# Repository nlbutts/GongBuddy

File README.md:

# GongBuddy

LoRa radio transmitter with accel/gyro to detect impacts on a gong

DIO5 = ModeReady
DIO4 = CadDetected
DIO3 = CadDone
DIO2 = FhssChangeChannel
DIO1 = RxTimeout
DIO0 = RxDone

Mapping of DIO to the LEDs
DIO3 = CadDone
DIO4 = CadDetected
DIO0 = RxDone
DIO1 = RxTimeout
DIO2 = FhssChangeChannel
DIO5 = ModeReady

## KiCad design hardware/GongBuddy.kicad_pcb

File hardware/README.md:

Designed for this enclosure
https://www.hammfg.com/electronics/small-case/extruded/1455
1455D601BK

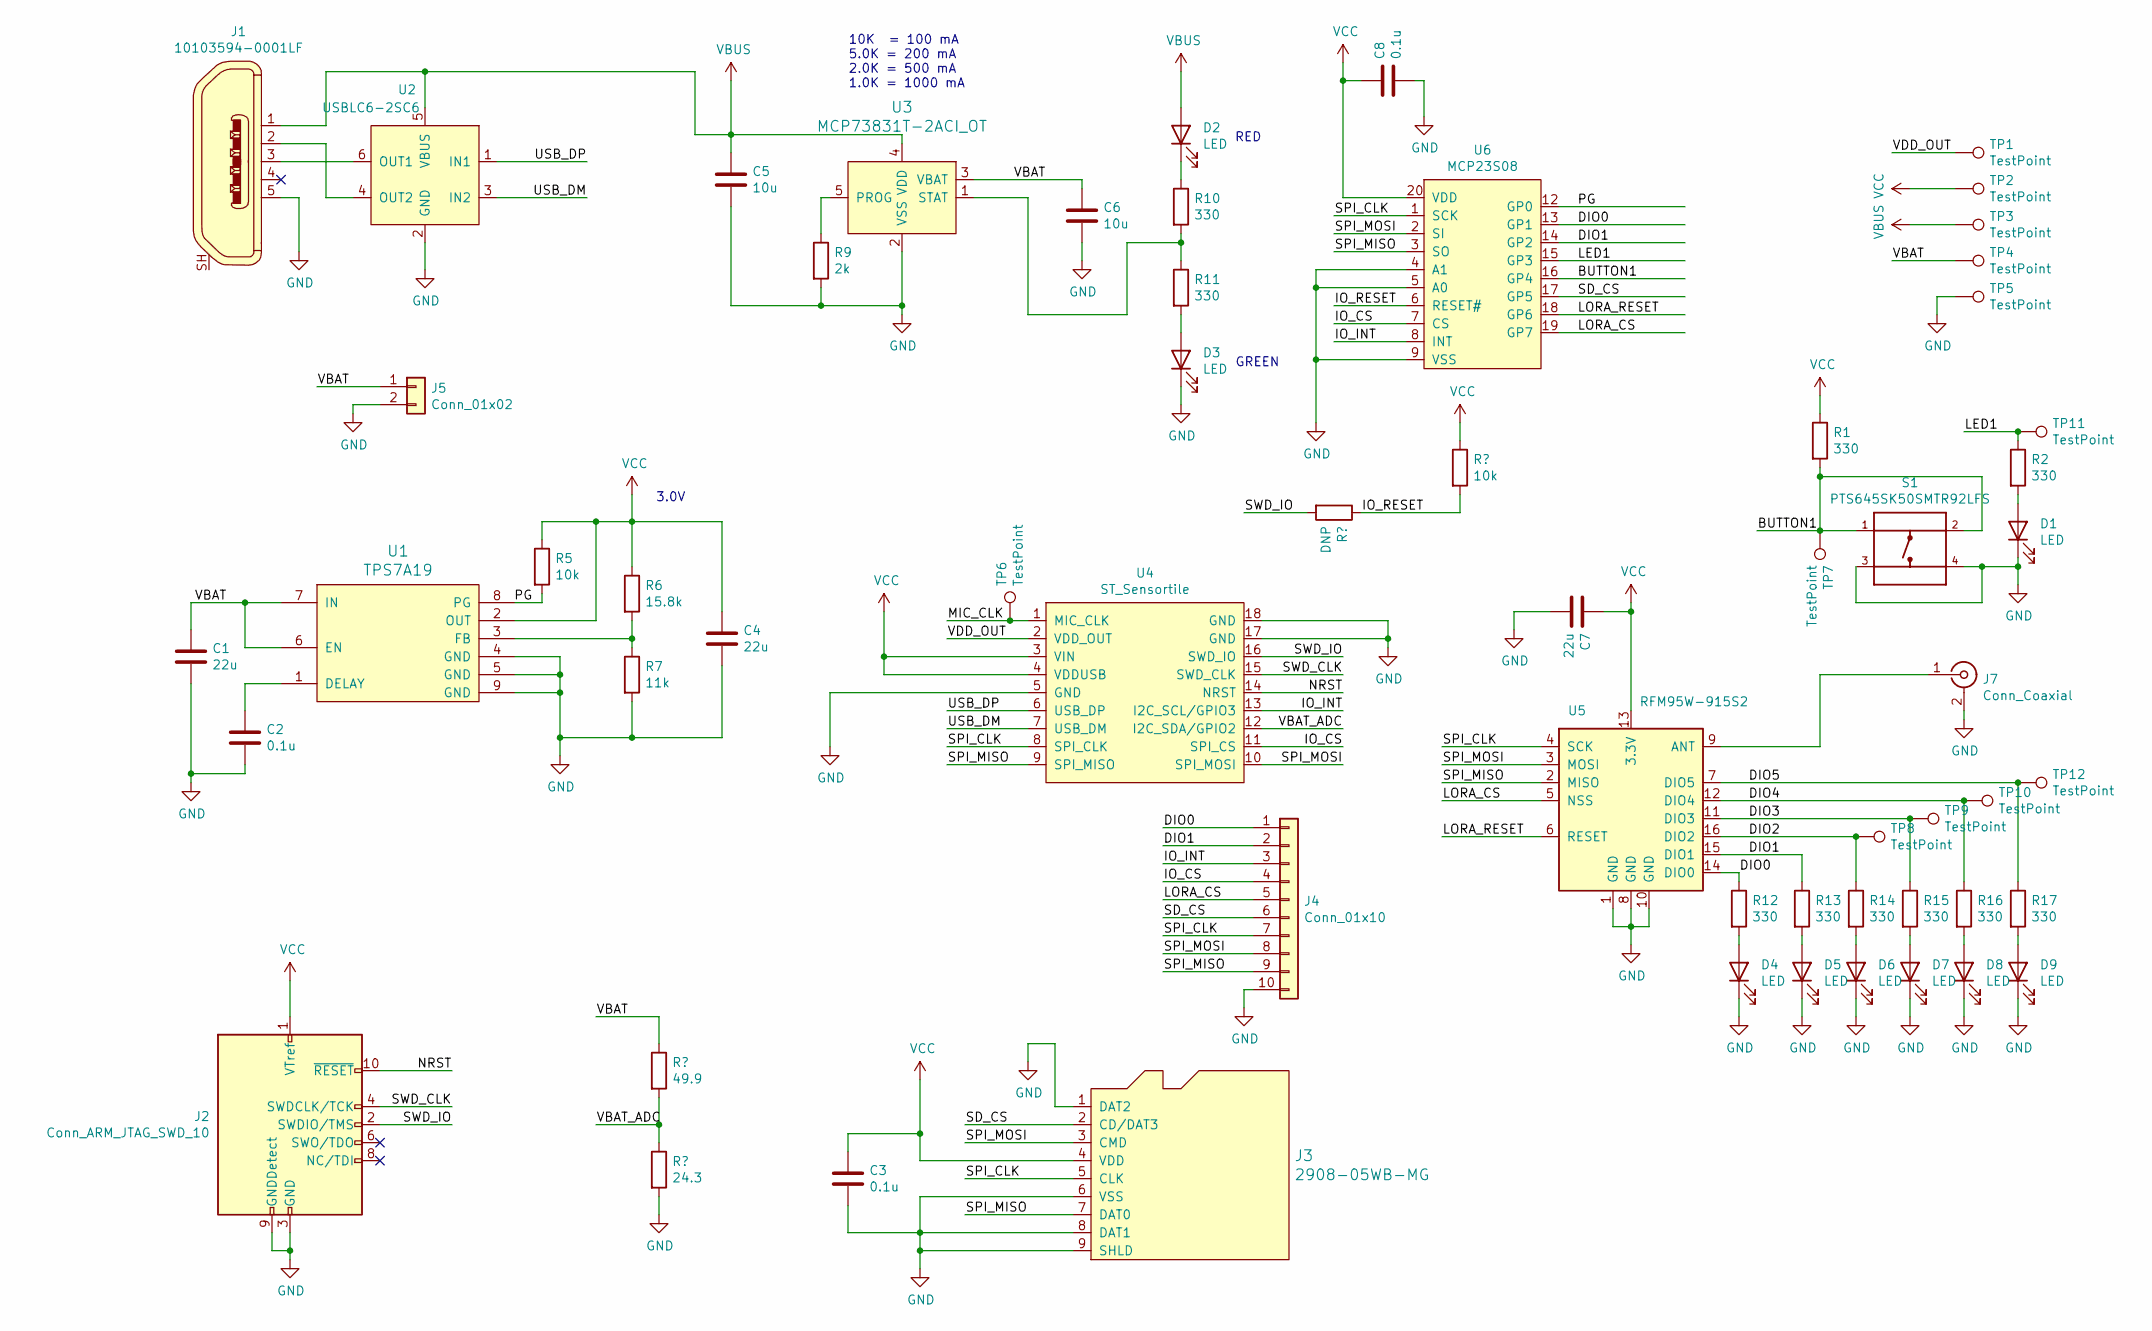
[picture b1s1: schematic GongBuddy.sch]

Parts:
C1, C4: 22u; C_1206_3216Metric
C2, C3, C8: 0.1u; C_0603_1608Metric
C5, C6: 10u; C_0603_1608Metric
C7: 22u; C_0603_1608Metric
D1, D2, D3, D4, D5, D6, D7, D8, D9: LED; LED_0603_1608Metric
J1: 10103594-0001LF; USB_Micro_B_Female_10103594-0001LF; MPN 10103594-0001LF; Digi-Key_PN 609-4050-1-ND
J2: Conn_ARM_JTAG_SWD_10; CortexSWD
J3: 2908-05WB-MG; MicroSD_2908-05WB-MG; MPN 2908-05WB-MG; Digi-Key_PN 3M5607CT-ND
J4: Conn_01x10; PinHeader_1x10_P2.54mm_Vertical
J5: Conn_01x02; JST_PH_B2B-PH-K_1x02_P2.00mm_Vertical
J7: Conn_Coaxial; SAMTEC_SMA-J-P-H-ST-EM1
R1, R2, R10, R11, R12, R13, R14, R15, R16, R17: 330; R_0603_1608Metric
R5: 10k; R_0603_1608Metric
R6: 15.8k; R_0603_1608Metric
R7: 11k; R_0603_1608Metric
R9: 2k; R_0603_1608Metric
S1: PTS645SK50SMTR92LFS; SW_PTS645SK50SMTR92LFS
TP1, TP2, TP3, TP4, TP5, TP6, TP7, TP8, TP9, TP10, TP11, TP12: TestPoint; TestPoint_Pad_D1.0mm
U1: TPS7A19; IC_DRV8601DRBT
U2: USBLC6-2SC6; SOT-23-6; Digikey 497-5235-2-ND
U3: MCP73831T-2ACI_OT; SOT-753; MPN MCP73831T-2ACI/OT; Digi-Key_PN MCP73831T-2ACI/OTCT-ND
U4: ST_Sensortile
U5: RFM95W-915S2; XCVR_RFM95W-915S2
U6: MCP23S08; SSOP-20_5.3x7.2mm_P0.65mm

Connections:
/BUTTON1: R1.2, S1.1, S1.2, TP7.1, U6.16 (GP4); also elsewhere on the board
/DIO0: J4.1, R12.1, U5.14 (DIO0), U6.13 (GP1)
/DIO1: J4.2, R13.1, U5.15 (DIO1), U6.14 (GP2)
/DIO2: R14.1, TP8.1, U5.16 (DIO2)
/DIO3: R15.1, TP9.1, U5.11 (DIO3)
/DIO4: R16.1, TP10.1, U5.12 (DIO4)
/DIO5: R17.1, TP12.1, U5.7 (DIO5)
/IO_CS: J4.4, U4.11 (SPI_CS), U6.7 (CS)
/IO_INT: J4.3, U4.13 (I2C_SCL/GPIO3), U6.8 (INT)
/IO_RESET: U6.6 (RESET#); also elsewhere on the board
/LED1: R2.1, TP11.1, U6.15 (GP3)
/LORA_CS: J4.5, U5.5 (NSS), U6.19 (GP7)
/LORA_RESET: U5.6 (RESET), U6.18 (GP6)
/MIC_CLK: TP6.1, U4.1 (MIC_CLK)
/NRST: J2.10 (~RESET~), U4.14 (NRST)
/PG: R5.2, U1.8 (PG), U6.12 (GP0)
/SD_CS: J3.2 (CD/DAT3), J4.6, U6.17 (GP5)
/SPI_CLK: J3.5 (CLK), J4.7, U4.8 (SPI_CLK), U5.4 (SCK), U6.1 (SCK)
/SPI_MISO: J3.7 (DAT0), J4.9, U4.9 (SPI_MISO), U5.2 (MISO), U6.3 (SO)
/SPI_MOSI: J3.3 (CMD), J4.8, U4.10 (SPI_MOSI), U5.3 (MOSI), U6.2 (SI)
/SWD_CLK: J2.4 (SWDCLK/TCK), U4.15 (SWD_CLK)
/SWD_IO: J2.2 (SWDIO/TMS), U4.16 (SWD_IO); also elsewhere on the board
/USB_DM: U2.3 (IN2), U4.7 (USB_DM)
/USB_DP: U2.1 (IN1), U4.6 (USB_DP)
/VBAT: C1.1, C6.1, J5.1, TP4.1, U1.6 (EN), U1.7 (IN), U3.3 (VBAT); also elsewhere on the board
/VBAT_ADC: U4.12 (I2C_SDA/GPIO2); also elsewhere on the board
GND: C1.2, C2.2, C3.2, C4.2, C5.2, C6.2, C7.2, C8.2, D1.1 (K), D3.1 (K), D4.1 (K), D5.1 (K), D6.1 (K), D7.1 (K), D8.1 (K), D9.1 (K), J1.5, J2.3 (GND), J2.5 (GND), J2.9 (GNDDetect), J3.1 (DAT2), J3.6 (VSS), J3.8 (DAT1), J3.9 (SHLD), J4.10, J5.2, J7.2 (Ext), R7.2, R9.2, S1.3, S1.4, TP5.1, U1.4 (GND), U1.5 (GND), U1.9 (GND), U1.10, U1.11, U1.12, U1.13, U2.2 (GND), U3.2 (VSS), U4.5 (GND), U4.17 (GND), U4.18 (GND), U5.1 (GND), U5.8 (GND), U5.10 (GND), U6.4 (A1), U6.5 (A0), U6.9 (VSS); also elsewhere on the board
unnamed: C2.1, U1.1 (DELAY)
unnamed: D1.2 (A), R2.2
unnamed: D2.1 (K), R10.1
unnamed: D3.2 (A), R11.2
unnamed: D4.2 (A), R12.2
unnamed: D5.2 (A), R13.2
unnamed: D6.2 (A), R14.2
unnamed: D7.2 (A), R15.2
unnamed: D8.2 (A), R16.2
unnamed: D9.2 (A), R17.2
unnamed: J1.2, U2.4 (OUT2)
unnamed: J1.3, U2.6 (OUT1)
unnamed: J7.1 (In), U5.9 (ANT)
unnamed: R6.2, R7.1, U1.3 (FB)
unnamed: R9.1, U3.5 (PROG)
unnamed: R10.2, R11.1, U3.1 (STAT)
VBUS: C5.1, D2.2 (A), J1.1, TP3.1, U2.5 (VBUS), U3.4 (VDD)

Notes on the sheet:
10K = 100 mA 5.0K = 200 mA 2.0K = 500 mA 1.0K = 1000 mA
RED
GREEN
3.0V

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
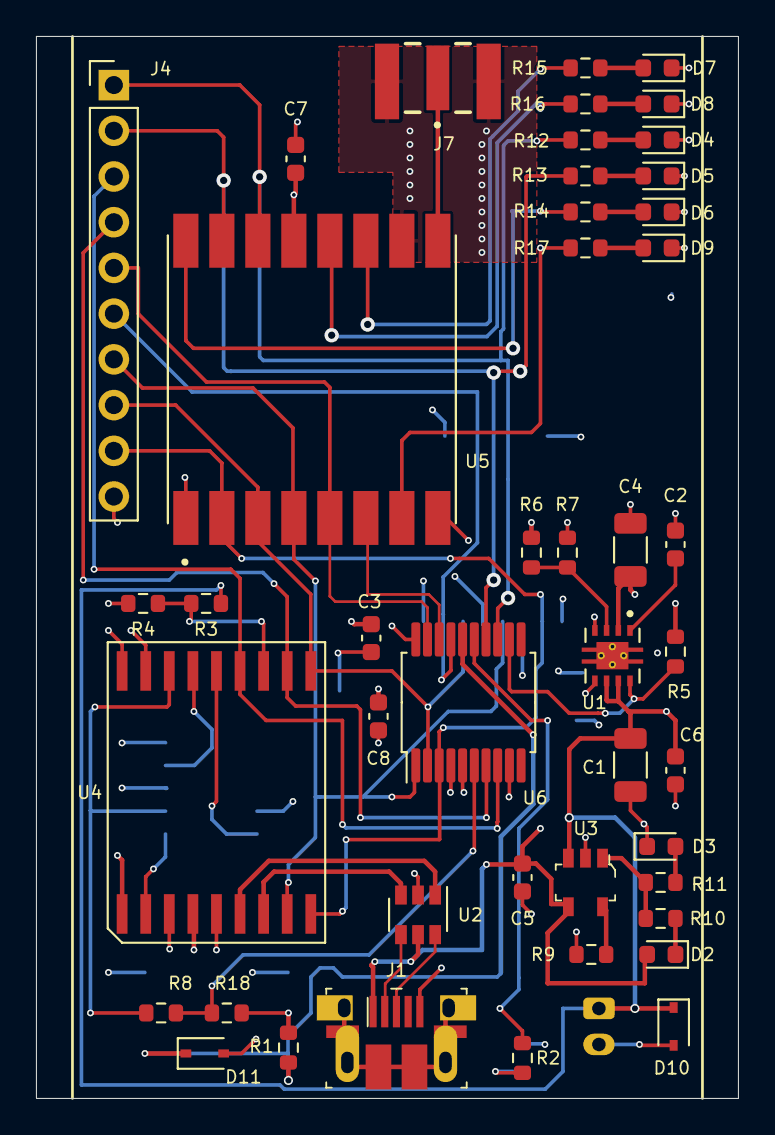
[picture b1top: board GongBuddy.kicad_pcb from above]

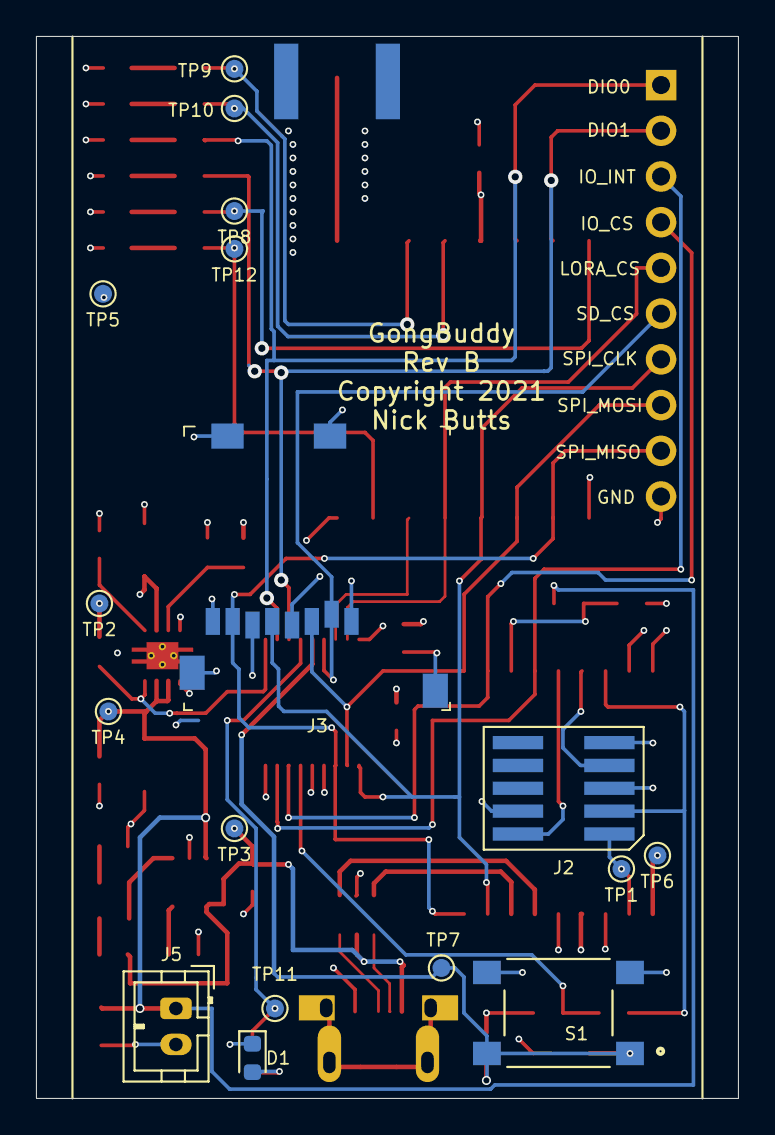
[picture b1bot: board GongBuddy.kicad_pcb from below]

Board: 4 copper layers, 39.0 x 59.0 mm, 62 parts (17 on the bottom side), 46 nets.

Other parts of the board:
D10, D11: DESD5V0U1BA-7; D_SOD-323
R3: 49.9; R_0603_1608Metric
R4: 24.3; R_0603_1608Metric
R8: DNP; R_0603_1608Metric
R18: 10k; R_0603_1608Metric

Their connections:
/BUTTON1: D11.1; also elsewhere on the board
/IO_RESET: R8.1, R18.2; also elsewhere on the board
/SWD_IO: R8.2; also elsewhere on the board
/VBAT: D10.1, R3.1; also elsewhere on the board
/VBAT_ADC: R3.2, R4.1; also elsewhere on the board
GND: D10.2, D11.2, R4.2; also elsewhere on the board

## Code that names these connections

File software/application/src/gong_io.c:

#include <stdint.h>
#include "mcp23S08.h"
#include "main.h"

#define IO_PG           0x01
#define IO_DIO0         0x02
#define IO_DIO1         0x04
#define IO_LED          0x08
#define IO_BUTTON       0x10
#define IO_SD_CS        0x20
#define IO_LORA_RESET   0x40
#define IO_LORA_CS      0x80

static void   *_spi;

static int write_spi(uint8_t * data, uint8_t len)
{
    HAL_GPIO_WritePin(IO_CS_GPIO_Port, IO_CS_Pin, 0);
    HAL_SPI_Transmit(_spi, data, len, 1000);
    HAL_GPIO_WritePin(IO_CS_GPIO_Port, IO_CS_Pin, 1);
    return 0;
}

static int tx_rx_spi(uint8_t * txdata, uint8_t * rxdata, uint8_t len)
{
    HAL_GPIO_WritePin(IO_CS_GPIO_Port, IO_CS_Pin, 0);
    HAL_SPI_TransmitReceive(_spi, txdata, rxdata, len, 100);
    HAL_GPIO_WritePin(IO_CS_GPIO_Port, IO_CS_Pin, 1);
    return 0;
}

void gong_io_init(void * spi)
{
    struct mcp23s08_cfg cfg = {0};
    _spi = spi;
    cfg.iodir = 0x17;
    cfg.write_spi = &write_spi;
    cfg.tx_rx_spi = &tx_rx_spi;
    mcp23s08_init(&cfg);
    mcp23s08_set_pin(0xFF);
}

void gong_io_set_led(int high)
{
    if (high)
        mcp23s08_set_pin(IO_LED);
    else
        mcp23s08_clear_pin(IO_LED);
}

void gong_io_set_sd_cs(int high)
{
    if (high)
        mcp23s08_set_pin(IO_SD_CS);
    else
        mcp23s08_clear_pin(IO_SD_CS);
}

void gong_io_set_lora_reset(int high)
{
    if (high)
        mcp23s08_set_pin(IO_LORA_RESET);
    else
        mcp23s08_clear_pin(IO_LORA_RESET);
}

void gong_io_set_lora_cs(int high)
{
    if (high)
        mcp23s08_set_pin(IO_LORA_CS);
    else
        mcp23s08_clear_pin(IO_LORA_CS);
}

int gong_io_read_pg()
{
    int value;
    int pins = mcp23s08_read_inputs();
    if (pins >= 0)
        value = pins & IO_PG;
    else
        value = pins;
    return value;
}

int gong_io_read_dio0()
{
    int value;
    int pins = mcp23s08_read_inputs();
    if (pins >= 0)
        value = pins & IO_DIO0;
    else
        value = pins;
    return value;
}

int gong_io_read_dio1()
{
    int value;
    int pins = mcp23s08_read_inputs();
    if (pins >= 0)
        value = pins & IO_DIO1;
    else
        value = pins;
    return value;
}

int gong_io_read_button()
{
    int value;
    int pins = mcp23s08_read_inputs();
    if (pins >= 0)
        value = pins & IO_BUTTON;
    else
        value = pins;
    return value;
}

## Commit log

2020-10-17 Initial checkin.
2020-10-18 Finished the layout and routing.
2020-10-22 Tweaked the layout slightly.
2020-10-23 Refactor board to a 4 layer.
2020-10-24 Added software.
2020-10-25 Refactored to use CMake because Eclipse sucks.
2020-11-02 Updated the drivers and toolchain files.
2020-11-21 Updated part numbers.
2020-11-22 Updated the hardware files.
2020-11-26 Added the I2C mux. Data is recording to the SD card. LED flashes. Can talk to Lora Radio.
2020-11-26 Forgot the I2C expander file.
2020-12-25 Added LoRa code, many tweaks.
2020-12-31 Fixed a gitignore issue. Updated the linker files. But now SD will not work.
2021-01-01 System seems to be working and is stable again.
2021-01-02 System is pretty stable. Basic command line system in place.
2021-01-03 Added protobuf message definition for Lora and reprogramming.
2021-01-03 Have a system that will transmit the last 15 IMU samples via a Lora protobuf upon impact detection.
2021-01-09 Tried to speed up the the I2C expander. Changed LED toggling.
2021-01-10 RTOS give you N number of issues where N is the number of threads you start. Had an issue with the debug LED, which I happen to tie to the LORA CS, which then screws up the SD interface. All is good 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
2021-01-10 Fixed all known embedded bugs. Working on ZMQ interfaces.
2021-01-10 Added the Raspberry Pi lora2zmq script.
2021-02-28 Updated the protobufs to send unique ID.
2021-02-28 Updated protobuf and created a Python app to receive LoRa messages and insert them into the MongoDB.
2021-03-03 Have working settings being transmitted down to the board.
2021-03-20 Starting to plum in the reprogramming capability.
2021-03-21 Updated the code and python data to start supporting OTA reprogramming.
2021-03-22 Major updates to support reprogramming. The PI can transfer a file to the GB and the GB can write it into FLASH. Need to make the Pi update more robust.
2021-03-24 Added the image gen X86 tool and the libupdate library.
2021-04-03 Minor updates to accel G rating.
2021-04-04 Removed reprogramming for now.
2021-04-09 Removed limitation on threshold.
2021-05-07 Updated the mechanical design, step files, etc.
2021-05-10 Added more files.
2021-05-17 Tweaked layout based on integration with the enclosure.
2021-05-19 Added ESD diodes and cleaned up the silkscreen.
2021-05-19 Tweaked the RF lines.
2021-06-04 Added additional datasheets and the CAD drawings.
2021-07-11 Updated datasheets.
2021-07-11 Refactoring the software for rev B.
2021-07-11 Added the cubemx code.
2021-07-20 Updates for the Rev B design software.
2021-07-31 Removed the gong_io test into it's own file.
2021-07-31 Added the ability to include or exclude the SEGGER RTT code from a release build.
2021-08-09 Moved the Debug print statements into third-party. Added LORA code into project. Added ST Accel/Gyro driver.
2021-08-11 Added unit tests.
2021-09-07 Updated googletest to the latest, added as a submodule.
2021-09-07 Switched user_tasks over to cpp.
2021-09-18 Major refactor and unit test development. Started working on firmware reprogramming.
2021-10-01 Updated unit tests. Have a unit test were all FW is transmitted, but the CRC fails.
2021-10-10 Reverted to the CPP version of the CRC calcualtor.
2021-10-10 Working to get a good firmware image unit test to pass.
2021-10-10 The programming unit tests work for good and bad data.

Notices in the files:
hardware/GongBuddy.kicad_pcb:
Copyright 2021
